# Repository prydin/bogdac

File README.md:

# BogDAC - A no frills DAC board for ES9039Q2M

## Introduction
I like to keep things simple. Reading about people "improving" their DACs with femtosecond-precision clocks, re-clockers, hundreds of farads of capacitance and potting soil (yes, potting soil), I decided I wanted to create a bog standard
DAC board based on the ES9039Q2M chip. I wanted a small board that would just accept an I2S stream and I2C commands and output single-ended audio. 

## Design Overview
This is following my Bog Standard concept: Keep things simple, follow best practices and avoid audiophile fads. The chip is locked into software mode and asynchronous I2S (a.k.a. PCM) operations using a local 49.152MHz oscillator. This 
allows for a design with a very simple and short clock signal path and should (at least in my opinion) perform better than external clocks connected through wires. The output section is pretty much just the one suggested in the data sheet and
based on OPA1612. The +/- 12V power for the analog section is provided by a TPS7A39 regulator. The 3.3V power for the analog reference voltages and the digital power is fed by a LT3046 regulator. The L3046 can be fed either from a separate 5V
power input or from the 12V rail by installing a jumper. Please note that nothing should be plugged into the 5V inlet if the jumper is installed.

## Schematic

## Test results
I tested this using a QA403. While this is a superb piece of gear, it has its limitations compared to test equipment that costs 100 times more. Because of this, the lower bound of the THD I can measure is about 0.0001% and the lowest noise 
floor is just above -150dBV. In fact, the harmonic profile of a loopback measurement looks very similar to the results I'm getting, so my hypothesis is that almost all noise and distortion you see comes from the measurement setup and 
not the circuit.

A 1kHz tone at full volume yields this spectrum. The THD is about 0.00013# and the SNR sits at about 113dB. I think the actual numbers are a lot better. Anyone who wants to lend me a $50,000 audio analyzer? :)

Another interesting measurement is looking at the idle noise. This is the DAC fully enabled, but without an input signal. I'm running the board on a cheap lab supply. As you can see, there's virtually no hum and very low noise.
You can thank those fancy regulators for that!

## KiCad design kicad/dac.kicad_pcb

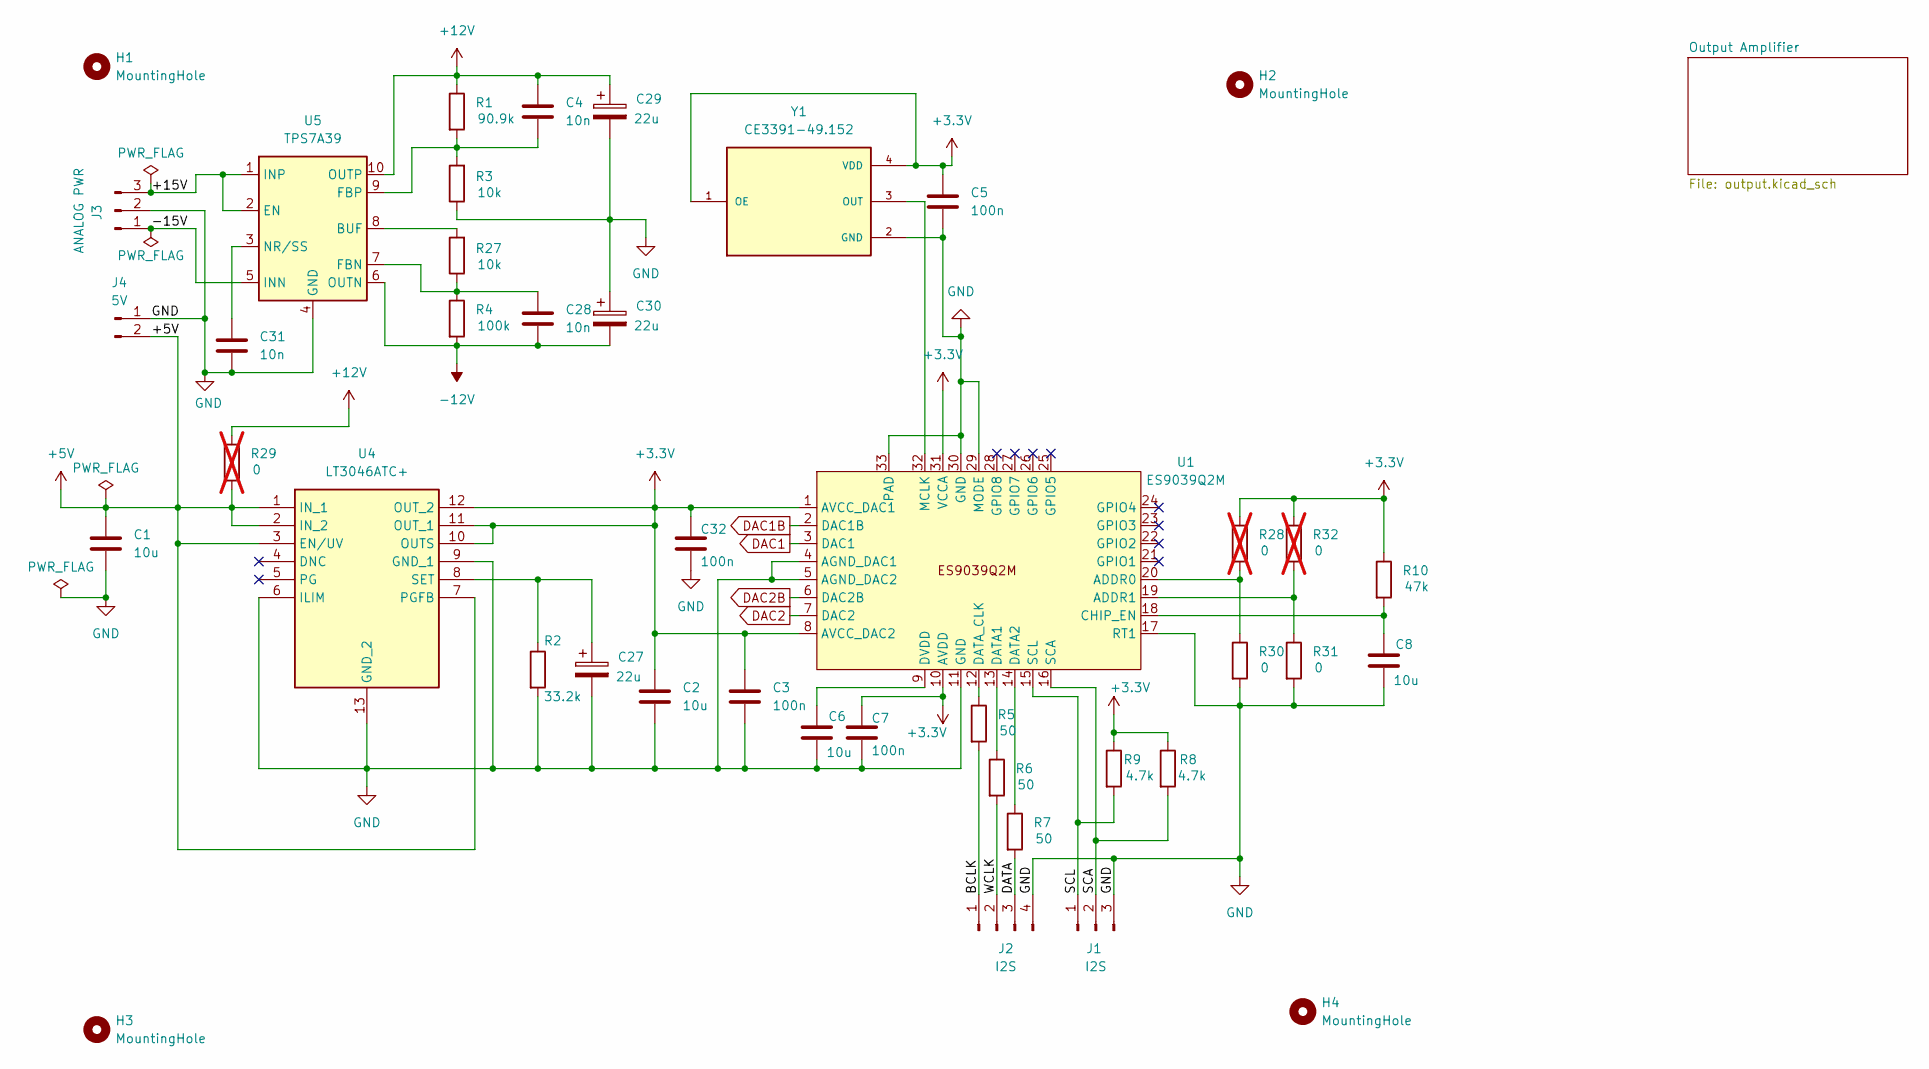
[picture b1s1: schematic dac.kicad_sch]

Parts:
C1, C2, C6, C8: 10u; C_0805_2012Metric
C3, C7, C32: 100n; C_0402_1005Metric
C4, C28, C31: 10n; C_0603_1608Metric
C5: 100n; C_0603_1608Metric
C27, C29, C30: 22u; CP_EIA-3216-10_Kemet-I_HandSolder
H1: MountingHole; MountingHole_3.2mm_M3
H2, H3, H4: MountingHole
J1: I2S; JST_PH_B3B-PH-K_1x03_P2.00mm_Vertical
J2: I2S; JST_PH_B4B-PH-K_1x04_P2.00mm_Vertical
J3: ANALOG PWR; JST_PH_B3B-PH-K_1x03_P2.00mm_Vertical
J4: 5V; JST_PH_B2B-PH-K_1x02_P2.00mm_Vertical
R1: 90.9k; R_0603_1608Metric_Pad0.98x0.95mm_HandSolder
R2: 33.2k; R_0603_1608Metric_Pad0.98x0.95mm_HandSolder
R3, R27: 10k; R_0603_1608Metric_Pad0.98x0.95mm_HandSolder
R4: 100k; R_0603_1608Metric_Pad0.98x0.95mm_HandSolder
R5, R6, R7: 50; R_0603_1608Metric_Pad0.98x0.95mm_HandSolder
R8, R9: 4.7k; R_0603_1608Metric_Pad0.98x0.95mm_HandSolder
R10: 47k; R_0603_1608Metric_Pad0.98x0.95mm_HandSolder
R28, R29, R32: 0; R_0603_1608Metric_Pad0.98x0.95mm_HandSolder; not fitted
R30, R31: 0; R_0603_1608Metric_Pad0.98x0.95mm_HandSolder
U1: ES9039Q2M; UFQFPN-32-1EP_5x5mm_P0.5mm_EP3.5x3.5mm
U4: LT3046ATC+; SON45P300X300X80-13N-D; Mouser Part Number 700-LT3046ATC+
U5: TPS7A39; Texas_S-PVSON-N10_ThermalVias
Y1: CE3391-49.152; Oscillator_SMD_Diodes_FN-4Pin_7.0x5.0mm; PARTREV NA

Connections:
+3.3V: C2.1, C3.1, C5.1, C7.1, C32.1, R8.1, R9.1, R10.1, R28.1, R32.1, U1.1 (AVCC_DAC1), U1.8 (AVCC_DAC2), U1.10 (AVDD), U1.31 (VCCA), U4.10 (OUTS), U4.11 (OUT_1), U4.12 (OUT_2), Y1.1 (OE), Y1.4 (VDD)
+5V: C1.1, J4.2, R29.2, U4.1 (IN_1), U4.2 (IN_2), U4.3 (EN/UV), U4.7 (PGFB)
+12V: C4.1, C29.1, R1.1, R29.1, U5.10 (OUTP); also elsewhere on the board
-12V: C28.2, C30.2, R4.2, U5.6 (OUTN); also elsewhere on the board
/+15V: J3.3, U5.1 (INP), U5.2 (EN)
/-15V: J3.1, U5.5 (INN)
/BCLK: J2.1, R5.2
/DATA: J2.3, R7.2
/SCA: J1.2, R8.2, U1.16 (SCA)
/SCL: J1.1, R9.2, U1.15 (SCL)
/WCLK: J2.2, R6.2
DAC1: U1.3 (DAC1); also elsewhere on the board
DAC1B: U1.2 (DAC1B); also elsewhere on the board
DAC2: U1.7 (DAC2); also elsewhere on the board
DAC2B: U1.6 (DAC2B); also elsewhere on the board
GND: C1.2, C2.2, C3.2, C5.2, C6.2, C7.2, C8.2, C27.2, C29.2, C30.1, C31.2, C32.2, J1.3, J2.4, J3.2, J4.1, R2.2, R3.1, R30.2, R31.2, U1.4 (AGND_DAC1), U1.5 (AGND_DAC2), U1.11 (GND), U1.17 (RT1), U1.29 (MODE), U1.30 (GND), U1.33 (PAD), U4.6 (ILIM), U4.9 (GND_1), U4.13 (GND_2), U5.4 (GND), U5.11 (GND), Y1.2 (GND); also elsewhere on the board
unnamed: R28.2, R30.1, U1.20 (ADDR0)
unnamed: R31.1, R32.2, U1.19 (ADDR1)
unnamed: C8.1, R10.2, U1.18 (CHIP_EN)
unnamed: R6.1, U1.13 (DATA1)
unnamed: R7.1, U1.14 (DATA2)
unnamed: R5.1, U1.12 (DATA_CLK)
unnamed: C6.1, U1.9 (DVDD)
unnamed: U1.32 (MCLK), Y1.3 (OUT)
unnamed: C27.1, R2.1, U4.8 (SET)
unnamed: R27.2, U5.8 (BUF)
unnamed: C28.1, R4.1, R27.1, U5.7 (FBN)
unnamed: C4.2, R1.2, R3.2, U5.9 (FBP)
unnamed: C31.1, U5.3 (NR/SS)

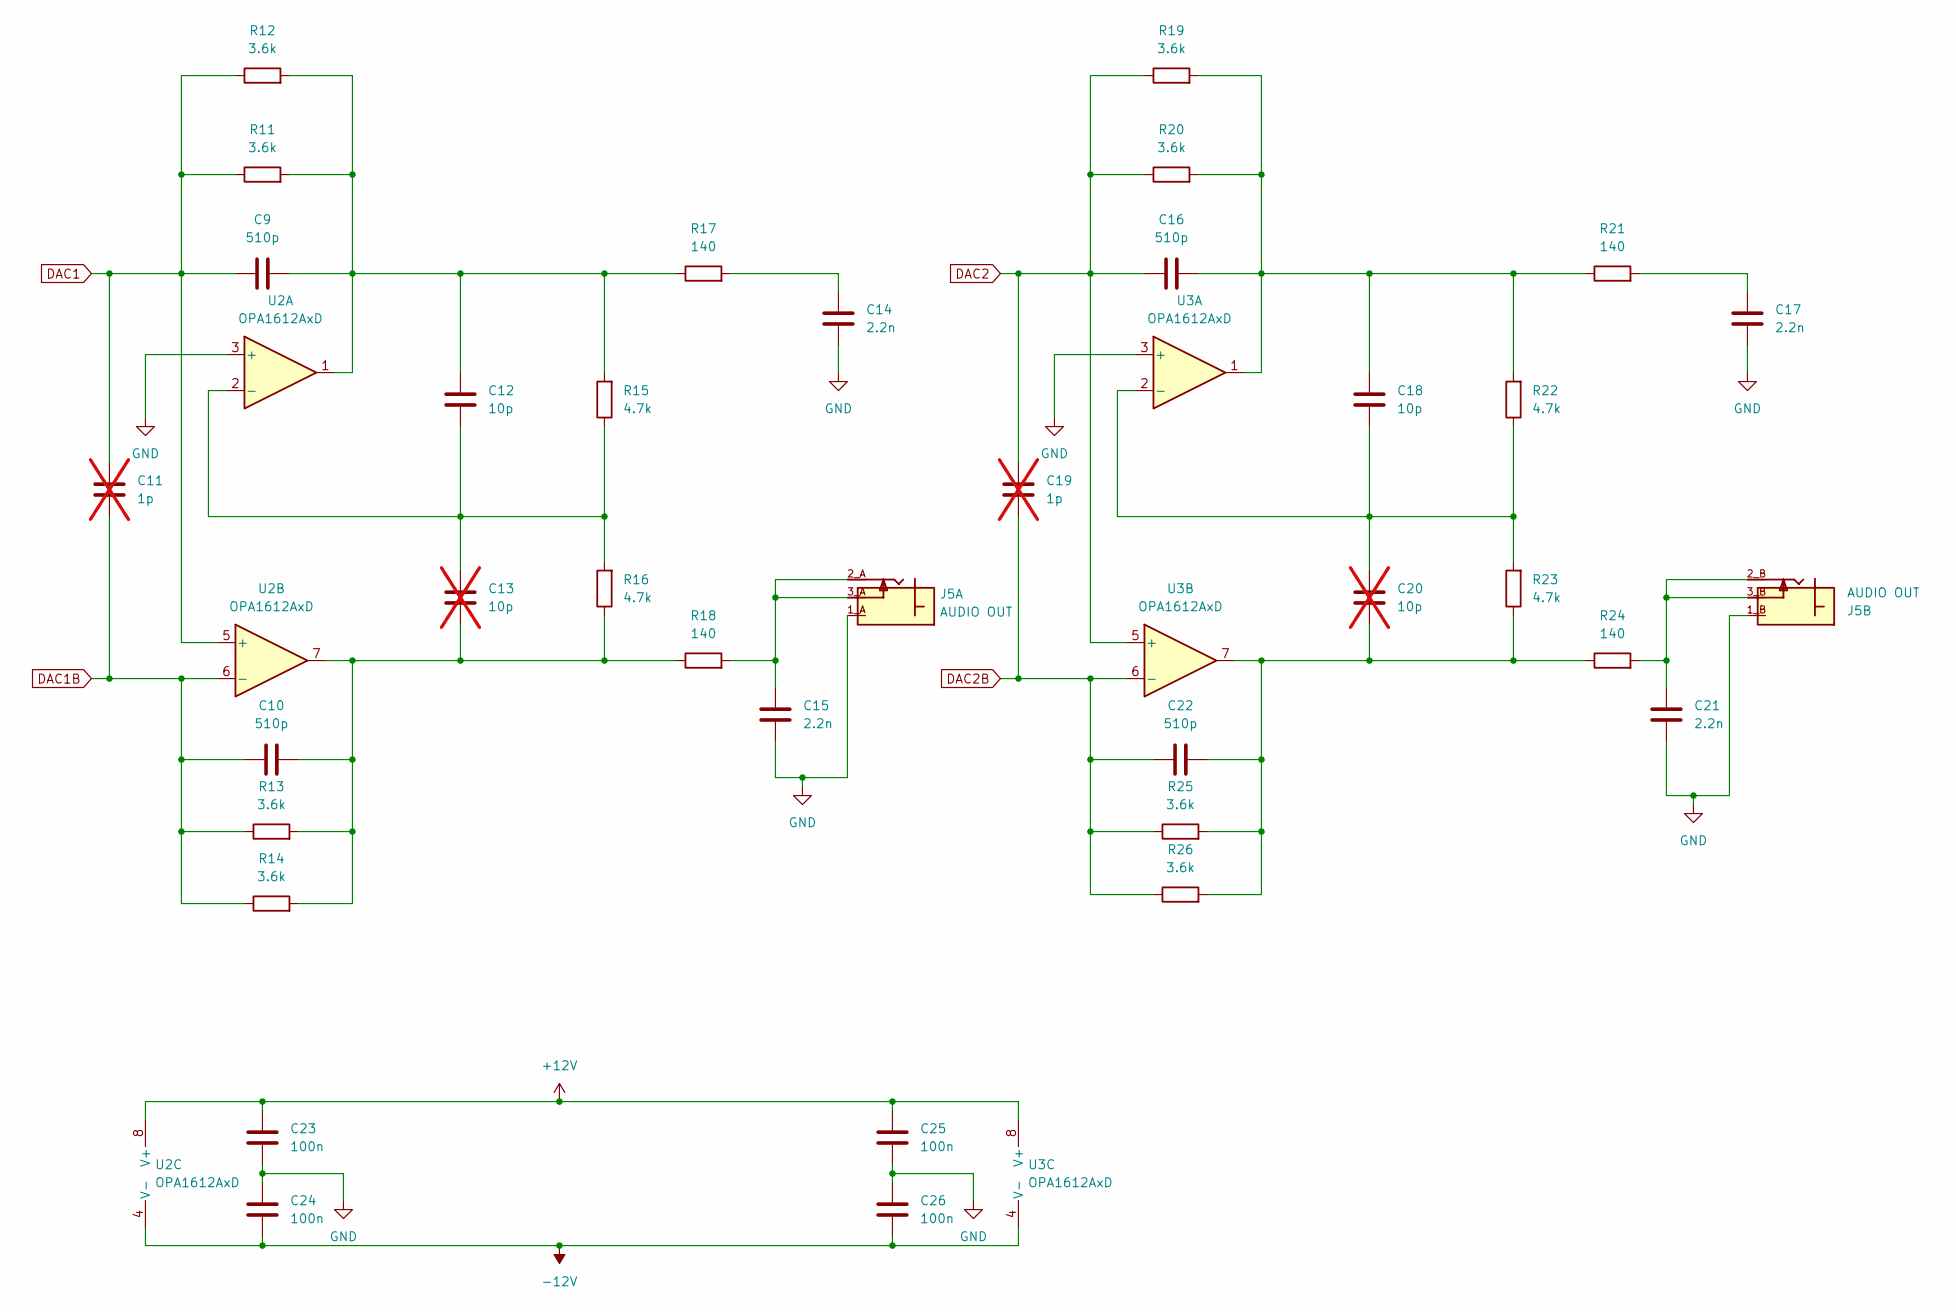
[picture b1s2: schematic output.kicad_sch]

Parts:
C9, C10, C16, C22: 510p; C_0603_1608Metric
C11, C19: 1p; C_0603_1608Metric; not fitted
C12, C18: 10p; C_0603_1608Metric
C13, C20: 10p; C_0603_1608Metric; not fitted
C14, C15, C17, C21: 2.2n; C_0603_1608Metric
C23, C24, C25, C26: 100n; C_0603_1608Metric
J5: AUDIO OUT; SWITCHCRAFT_PJRAN2X1U01AUX
R11, R12, R13, R14, R19, R20, R25, R26: 3.6k; R_0603_1608Metric_Pad0.98x0.95mm_HandSolder
R15, R16, R22, R23: 4.7k; R_0603_1608Metric_Pad0.98x0.95mm_HandSolder
R17, R18, R21, R24: 140; R_0603_1608Metric_Pad0.98x0.95mm_HandSolder
U2, U3: OPA1612AxD; SOIC-8_3.9x4.9mm_P1.27mm

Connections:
+12V: C23.2, C25.2, U2.8 (V+), U3.8 (V+); also elsewhere on the board
-12V: C24.1, C26.1, U2.4 (V-), U3.4 (V-); also elsewhere on the board
DAC1: C9.1, C11.2, R11.1, R12.1, U2.5 (+); also elsewhere on the board
DAC1B: C10.1, C11.1, R13.1, R14.1, U2.6 (-); also elsewhere on the board
DAC2: C16.1, C19.2, R19.1, R20.1, U3.5 (+); also elsewhere on the board
DAC2B: C19.1, C22.1, R25.1, R26.1, U3.6 (-); also elsewhere on the board
GND: C14.1, C15.1, C17.1, C21.1, C23.1, C24.2, C25.1, C26.2, J5.1_A, J5.1_B, U2.3 (+), U3.3 (+); also elsewhere on the board
unnamed: C10.2, C13.1, R13.2, R14.2, R16.1, R18.1, U2.7
unnamed: C9.2, C12.2, R11.2, R12.2, R15.2, R17.1, U2.1
unnamed: C14.2, R17.2
unnamed: C15.2, J5.2_A, J5.3_A, R18.2
unnamed: C16.2, C18.2, R19.2, R20.2, R21.1, R22.2, U3.1
unnamed: C17.2, R21.2
unnamed: C20.1, C22.2, R23.1, R24.1, R25.2, R26.2, U3.7
unnamed: C21.2, J5.2_B, J5.3_B, R24.2
unnamed: C12.1, C13.2, R15.1, R16.2, U2.2 (-)
unnamed: C18.1, C20.2, R22.1, R23.2, U3.2 (-)

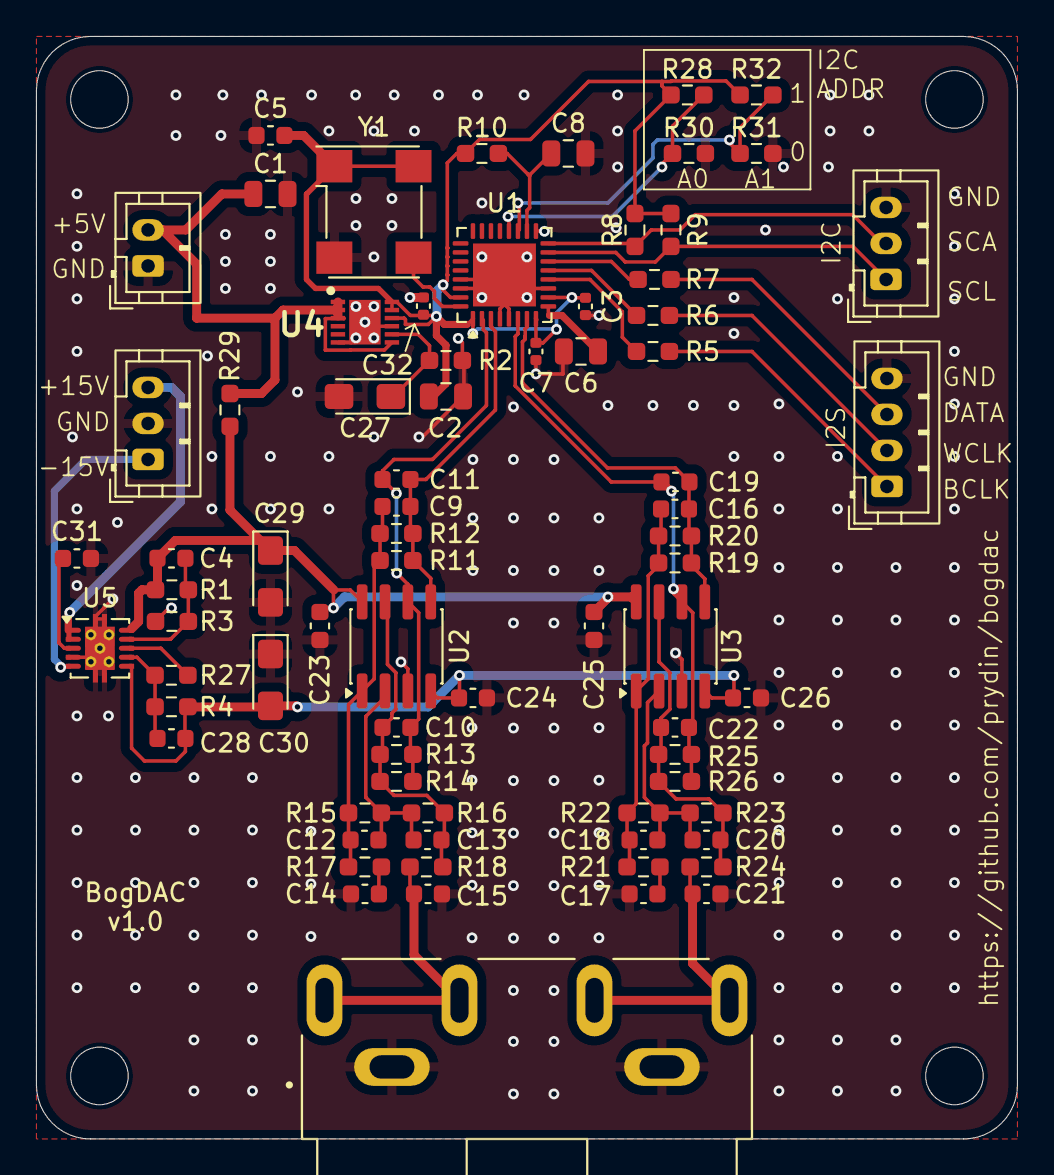
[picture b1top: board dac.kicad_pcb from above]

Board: 4 copper layers, 54.5 x 61.2 mm, 79 parts (0 on the bottom side), 39 nets.

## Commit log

2026-02-08 Initialize README with project details and design
    Added detailed project description and design overview.
2026-02-08 Removed obsolete gerber files
2026-02-10 Revise README with design overview and schematics
    Updated section headings and added schematic images.
2026-02-10 Added images and small PCB changes
2026-02-10 Added images
2026-02-10 Change schematic images from JPG to PNG
    Updated schematic image formats from JPG to PNG.
2026-02-11 V1.0
2026-02-11 Document test results and measurements in README
    Added test results and measurements for QA403 testing.
2026-02-11 Added gerber
